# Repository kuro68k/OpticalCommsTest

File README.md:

# OpticalCommsTest
Communicate with an MCU optically from Javascript/web browser

One way communication between Javascript running in a browser and a microcontroller. This is just a prototype/experiment.

An area of the screen is flashed black/white, with data encoded via one of two methods I am experimenting with: pulse width and RS-232/UART. A simple photodiode is used to detect the colour of the screen. A typical configuration would have the diode connected to a comparator. One input would be the signal directly, the other would be a low pass filtered version with slight offset allowing for automatic gain setting. A lower cost option might remove the AGC and replce with a trim pot.

The Javascript code uses frame sync to transmit data as fast as the screen refresh will allow, although that is still relatively slow. With pulse-width encoding the average data rate is around 25 bps on a common 60Hz display. With RS-232/UART encoding it's 48 bps (8n1).

In either case auto-bauding is required. The screen refresh rate can vary, and my goal is to support microcontrollers running from a low accuracy RC oscillator.

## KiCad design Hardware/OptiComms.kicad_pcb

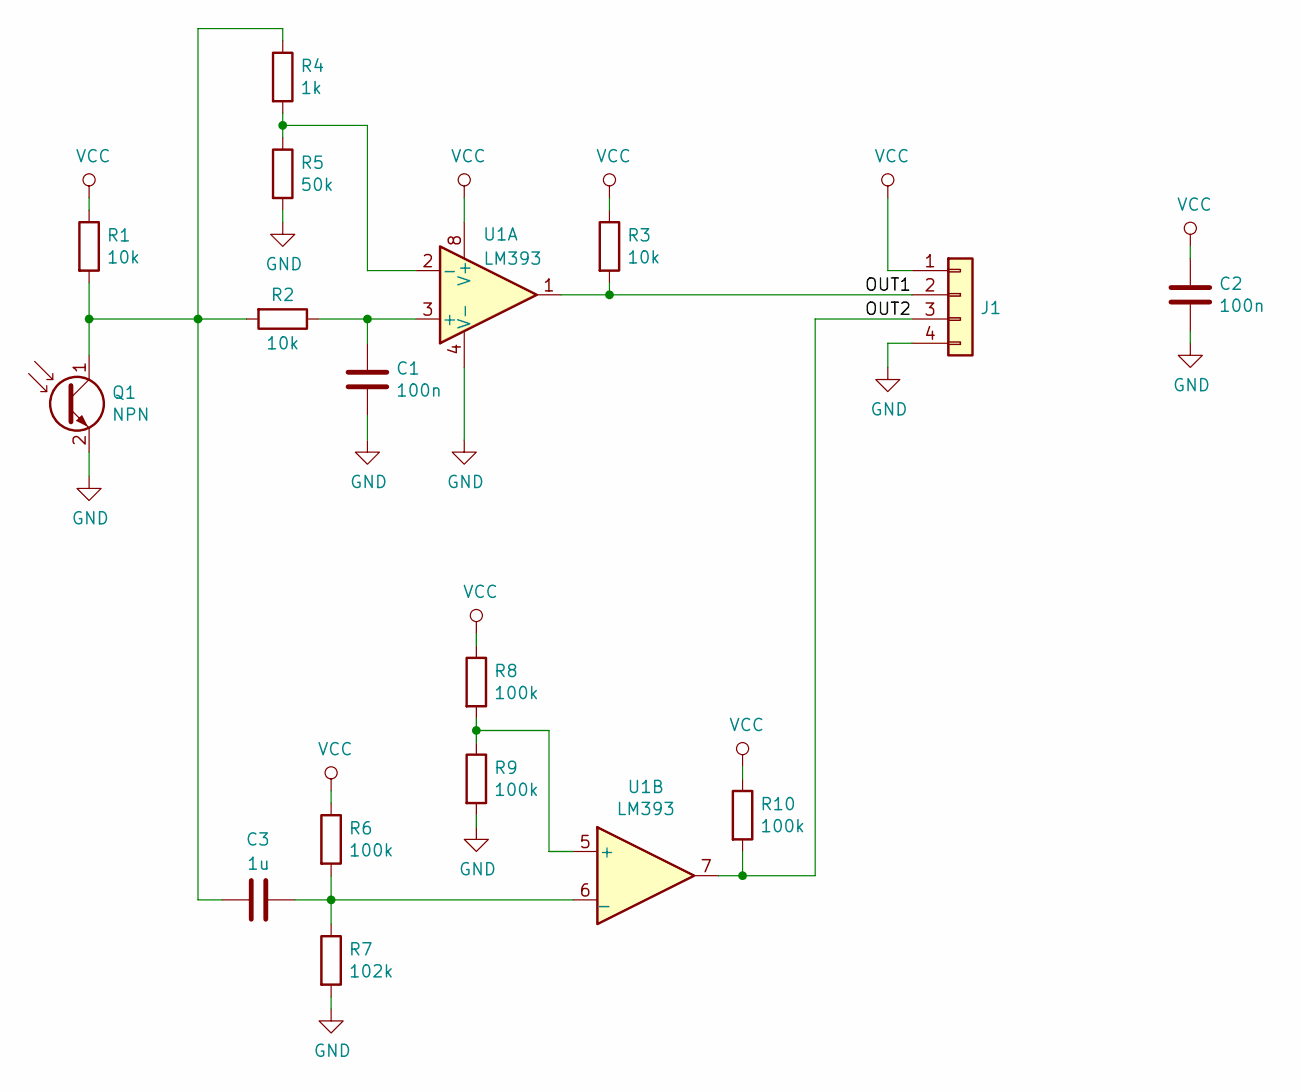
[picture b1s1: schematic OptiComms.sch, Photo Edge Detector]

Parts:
C1, C2: 100n; C_0603_1608Metric_Pad1.05x0.95mm_HandSolder
C3: 1u; C_0603_1608Metric_Pad1.05x0.95mm_HandSolder
J1: Conn_01x04; PinHeader_1x04_P2.54mm_Vertical
Q1: NPN; LED_D5.0mm
R1, R2, R3: 10k; R_0603_1608Metric_Pad1.05x0.95mm_HandSolder
R4: 1k; R_0603_1608Metric_Pad1.05x0.95mm_HandSolder
R5: 50k; R_0603_1608Metric_Pad1.05x0.95mm_HandSolder
R6, R8, R9, R10: 100k; R_0603_1608Metric_Pad1.05x0.95mm_HandSolder
R7: 102k; R_0603_1608Metric_Pad1.05x0.95mm_HandSolder
U1: LM393; SOIC-8_3.9x4.9mm_P1.27mm

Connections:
/OUT1: J1.2, R3.2, U1.1
/OUT2: J1.3, R10.2, U1.7
GND: C1.2, C2.2, J1.4, Q1.2 (E), R5.2, R7.2, R9.2, U1.4 (V-)
unnamed: C1.1, R2.1, U1.3 (+)
unnamed: C3.1, Q1.1 (C), R1.2, R2.2, R4.1
unnamed: C3.2, R6.2, R7.1, U1.6 (_)
unnamed: R4.2, R5.1, U1.2 (-)
unnamed: R8.2, R9.1, U1.5 (+)
VCC: C2.1, J1.1, R1.1, R3.1, R6.1, R8.1, R10.1, U1.8 (V+)

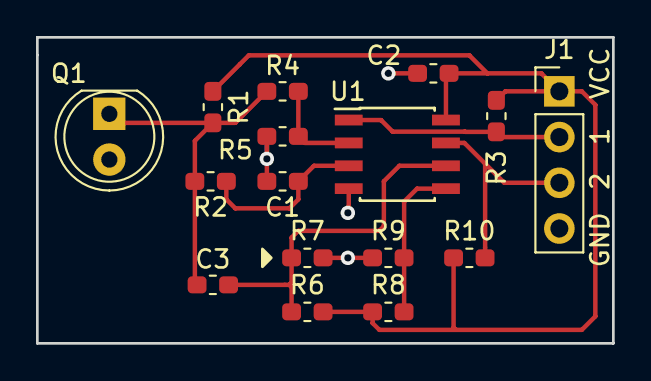
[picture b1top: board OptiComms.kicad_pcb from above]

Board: 2 copper layers, 32.0 x 17.0 mm, 16 parts (0 on the bottom side), 9 nets.

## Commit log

2019-06-22 Accurately reads bitstream
2019-06-23 progmem strings
2019-07-12 Test hardware
2019-08-02 AC coupled test hardware
2019-08-12 Sonic comms
2019-11-27 Research

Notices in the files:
Hardware/OptiComms.sch:
Licence: GPL V3
